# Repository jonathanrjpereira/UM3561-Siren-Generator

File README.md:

# UM3561-Siren-Generator
Can play either a Police Siren, Ambulance Siren or Fire Engine Siren when triggered.

**Full Video:**

**Order PCB:**  [PCBWay](https://bit.ly/2vg0xno)    

## Electronic Components
| Qty | Component | Buy |
| ------------- | ------------- | ------------- |
| 1 | UM3561 |[AliExpress](http://s.click.aliexpress.com/e/ckC9oWJA) |
| 1 | BC547 NPN Transistor |[AliExpress](http://s.click.aliexpress.com/e/bpL0Irsk) |
| 1 | 220KΩ Resistor |[AliExpress](http://s.click.aliexpress.com/e/bh4eqrQs) |
| 2 | 220Ω Resistor |[AliExpress](http://s.click.aliexpress.com/e/bh4eqrQs) |
| 1 | 5mm LED |[AliExpress](http://s.click.aliexpress.com/e/wuFpLXS) |
| 1 | SPDT Slider Switch |[AliExpress](http://s.click.aliexpress.com/e/bKFlazR2) |
| 1 | SP3T Slider Switch |[AliExpress](http://s.click.aliexpress.com/e/bZ3jBWuY) |
| 2 | 2-Pin Male Header Pins |[AliExpress](http://s.click.aliexpress.com/e/bIN5SJXw) |
| 1 | Speaker |[AliExpress](http://s.click.aliexpress.com/e/brMJh46c) |
| 1 | AA Battery Holder (2 Slot) |[AliExpress](http://s.click.aliexpress.com/e/c7Lm2Nm0) |
| 2 | AA Battery |[AliExpress](http://s.click.aliexpress.com/e/YMpokbA) |

| Tools | Buy |
|--|--|
|Soldering Iron|[AliExpress](http://s.click.aliexpress.com/e/E83bSJI) |
|Soldering Wire|[AliExpress](http://s.click.aliexpress.com/e/PdhB0nm) |

## Working
**UM3561:**

The UM3561 is a low-cost, low power CMOS LSI designed for use in toy applications. Since the integrated circuit
includes oscillating and selector circuits, a compact sound module can be constructed with only a few additional
components. The UM3561 contains a programmed mask ROM to electronically reproduce alarm sounds.

- Typical Operating Voltage = 3V
- 8-Pin DIP Package
- Power On Reset

**Circuit:**

Only one of the Siren tunes can be played at a time. This is determined on the basis of the position of the SP3T Slide switch.
The switch has three positions which will connect the common terminal with VCC, GND or NC in order to fulfill the Truth Table.

A dynamic speaker is driven with an external NPN transistor.
A SPDT switch is used to turn the circuit ON & OFF.

## Contributing🛠
Are you an engineer or hobbyist who has a great idea for a new feature in this project? Maybe you have a good idea for a bug fix? Feel free to grab our code & schematics from Github and tinker with it. Don't forget to smash ⭐️ & the Pull Request button.

[![alt text][1.1]][1] [![alt text][2.1]][2] [![alt text][3.1]][3]

[1.1]: https://github.com/jonathanrjpereira/Social-Media-README/blob/master/youtube.png (YouTube)
[2.1]: https://github.com/jonathanrjpereira/Social-Media-README/blob/master/instagram.png (Instagram)
[3.1]: https://github.com/jonathanrjpereira/Social-Media-README/blob/master/github.png (GitHub)

[1]: https://www.youtube.com/channel/UCRW-41O1vy98KKgJRQoYzdg
[2]: https://www.instagram.com/electroguruji/
[3]: https://github.com/jonathanrjpereira

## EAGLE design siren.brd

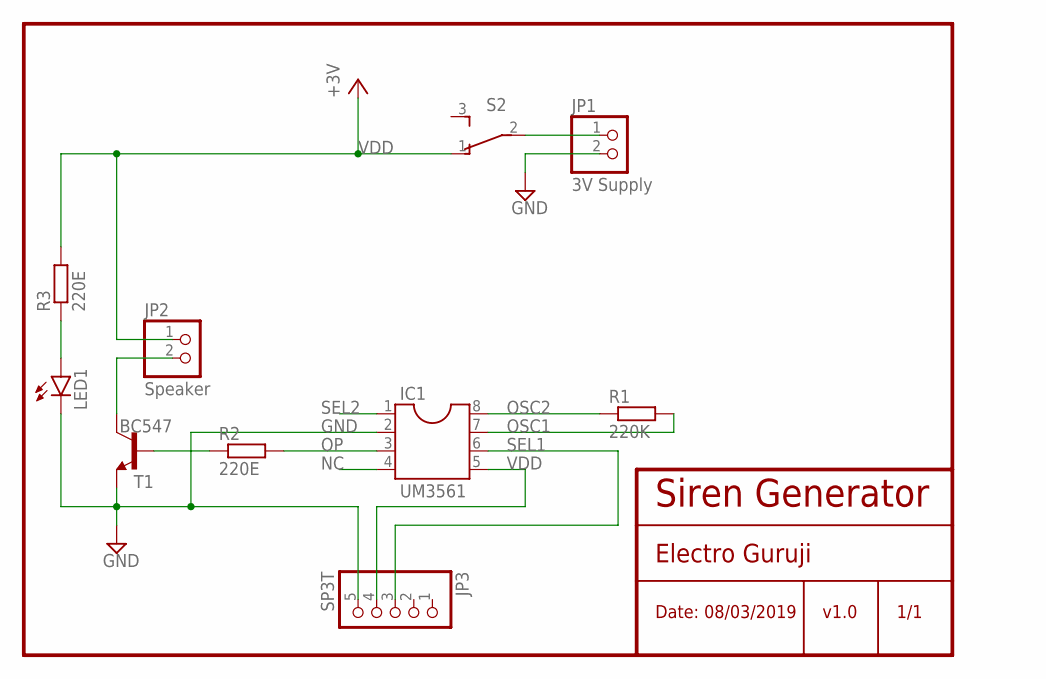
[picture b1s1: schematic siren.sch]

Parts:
IC1: UM3561; SOCKET-08
JP1: 3V Supply; 1X02
JP2: Speaker; 1X02
JP3: SP3T; 1X05
LED1: LED5MM
R1: 220K; 0204/5
R2, R3: 220E; 0204/5
S2: TL36YO; TL3XYO
T1: BC547; TO92-EBC

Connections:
GND: IC1.2, JP1.2, JP3.5, LED1.K (C), T1.E
unnamed: JP1.1, S2.2
unnamed: LED1.A, R3.1
unnamed: JP2.2, T1.C
unnamed: R2.1, T1.B
NC: IC1.4
OP: IC1.3, R2.2
OSC1: IC1.7, R1.2
OSC2: IC1.8, R1.1
SEL1: IC1.6, JP3.3
SEL2: IC1.1
VDD: IC1.5, JP2.1, JP3.4, R3.2, S2.1 (O)

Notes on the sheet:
Siren Generator
Electro Guruji
Date: 08/03/2019
v1.0
1/1

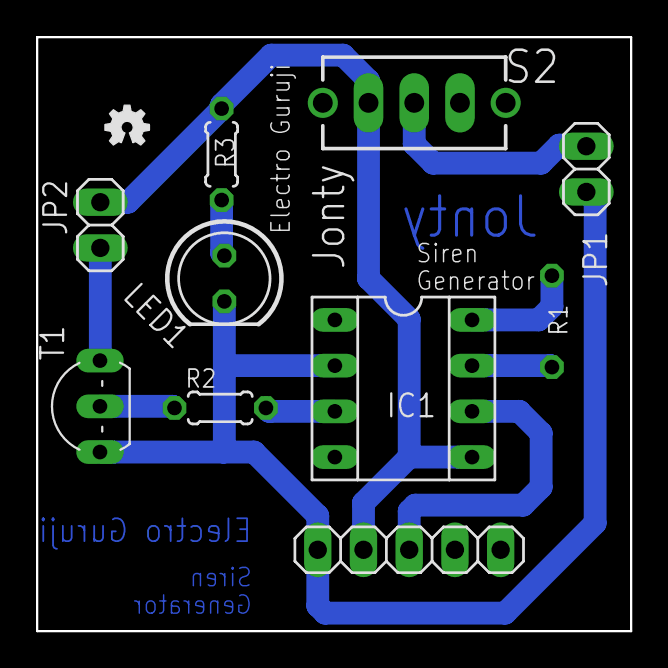
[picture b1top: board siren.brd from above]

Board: 2 copper layers, 33.0 x 33.0 mm, 11 parts (1 on the bottom side), 10 nets.

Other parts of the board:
U$1: OSHW-LOGO-MINI

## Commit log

2019-03-08 SP3T Switch
2019-03-09 SP3T replaced with 5 header pins
2019-03-23 NPN Transistor
2019-04-07 Photo
2019-04-07 delete
2019-04-22 Gerber Files

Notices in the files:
parts and their libraries:
SparkFun-Aesthetics: Licensing: Creative Commons ShareAlike 4.0 International - https://creativecommons.org/licenses/by-sa/4.0
